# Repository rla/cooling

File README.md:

# avrcooling

PC cooling controller for rotary cooling devices (fans/pumps). It has
the following features:

 * Supports 4 cooling devices.
 * Can disable devices that still run on minimal PWM.
 * Monitors devices RPM.
 * RPM measurement supports pulse stretching.
 * Supports 2 thermal sensors.
 * Error signal output.
 * Can be controlled/queried over RS-232 interface.
 * Command-line client to query/debug/control the device.
 * Hardware design and source code is MIT-licensed.

### Control algorithm

The control algorithm uses 2 [decision tables](http://en.wikipedia.org/wiki/Decision_table),
one per thermal sensor. Table rows contain the following information:

 * enabled - whether the control row is enable.
 * min_temp - lower bound for activating the control row.
 * max_temp - upper bound for activating the control row.
 * affect_fan0 - whether to apply the row to fan 0.
 * affect_fan1 - whether to apply the row to fan 1.
 * affect_fan2 - whether to apply the row to fan 2.
 * affect_fan3 - whether to apply the row to fan 3.
 * fan0_pwm - PWM value to apply for fan 0.
 * fan1_pwm - PWM value to apply for fan 1.
 * fan2_pwm - PWM value to apply for fan 2.
 * fan3_pwm - PWM value to apply for fan 3.

There are 5 rows in each table. The first row with
min_temp...max_temp range including the current temperature is used for
applying the control values.

All cooling fans start initially in disabled state and with
0 PWM. When a fan PWM is set to a value greater than 0 then the fan power is
enabled. When PWM is set to 0 then the fan is also powered down.

Control table rows are checked periodically. The rows can be
read and updated using the command-line PC app described below.

## Project structure

The project is divided into 3 subdirectories:

 * `avr` - source for microcontroller binary.
 * `hw` - physical hardware design.
 * `pc` - NodeJS command-line app for communication.

## Hardware

### Pin allocation

 * pin  1: reset, connected to VCC and protected by zener diode
 * pin  2: USART RX line (pullup?)
 * pin  3: USART TX line
 * pin  4: PD2, Error signal output
 * pin  5: PD3, OC2B, fan 4 PWM output
 * pin  6: PD4, not connected
 * pin  7: VCC
 * pin  8: GND
 * pin  9: XTAL 1
 * pin 10: XTAL 2
 * pin 11: PD5, OC0B, fan 2 PWM output
 * pin 12: PD6, OC0A, fan 1 PWM output
 * pin 13: PD7, not connected
 * pin 14: PB0, fan 1 enable
 * pin 15: PB1, fan 2 enable
 * pin 16: PB2, fan 3 enable
 * pin 17: PB3, fan 3 PWM output
 * pin 18: PB4, fan 4 enable
 * pin 19: PB5, not connected
 * pin 20: AVCC, connected to VCC through low-pass filter L1/C13
 * pin 21: AREF, analog reference, decoupled with 100nF cap C10
 * pin 22: GND
 * pin 23: PC0, ADC0, temperature sensor 1 input, low-pass filter R5/C7
 * pin 24: PC1, ADC1, temperature sensor 2 input, low-pass filter R3/C8
 * pin 25: PC2, fan 1 RPM input, pull-up, low-pass filter R10/C9
 * pin 26: PC3, fan 2 RPM input, pull-up, low-pass filter R9/C11
 * pin 27: PC4, fan 3 RPM input, pull-up, low-pass filter R8/C12
 * pin 28: PC5, fan 4 RPM input, pull-up, low-pass filter R7/C14

### Port directions

#### Port B

 * PB0 - output (fan 1 enable)
 * PB1 - output (fan 2 enable)
 * PB2 - output (fan 3 enable)
 * PB3 - output (fan 3 PWM)
 * PB4 - output (fan 4 enable)
 * PB5 - output (not connected)
 * PB6 - output (overriden by xtal)
 * PB7 - output (overriden by xtal)

#### Port C

 * PC0 - input (ADC)
 * PC1 - input (ADC)
 * PC2 - input (fan 1 RPM, pull-up)
 * PC3 - input (fan 2 RPM, pull-up)
 * PC4 - input (fan 3 RPM, pull-up)
 * PC5 - input (fan 4 RPM, pull-up)
 * PC6 - input (default reset config)
 * PC7 - not in circuit/registry

#### Port D

 * PD0 - output (overriden by USART)
 * PD1 - output (overriden by USART)
 * PD2 - output (error)
 * PD3 - output (fan 4 PWM)
 * PD4 - output (not connected)
 * PD5 - output (fan 2 PWM)
 * PD6 - output (fan 1 PWM)
 * PD7 - output (not connected)

### Full schematics

Full schematics in Eagle format can be found in the file `hw/schematics.sch`.

#### Part list

 * C1 10uF/16V
 * C2 100nF/63V 5mm
 * C3, C4 22pF/63V 2.54mm
 * C5 100nF/63V 5mm
 * C6 10uF/16V 5mm
 * C7, C8 10nF/100V 5mm
 * C9, C11, C12, C14 10nF/63V 5mm
 * C10 100nF/63V 5mm
 * C13 100nF/63V 5mm
 * D1 5.1V zener 7.62mm
 * D2, D3, D4, D5 2N4007
 * IC1 Atmega88 DIP28
 * R1, R2, R3, R4, R5, R6, R7, R8, R9, R10, R11 10k
 * Q1 12MHz
 * Q2, Q4, Q6, Q8 2N7000
 * Q3, Q5, Q7, Q9 IRF9530
 * L1 10uH
 * X3 molex power connector, [Farnell product page](http://uk.farnell.com/jsp/search/productdetail.jsp?SKU=1391827)
 * X6, X7, X8, X9 molex 47053-1000 headers, [Farnell product page](http://uk.farnell.com/jsp/search/productdetail.jsp?SKU=2313705)

### Board layout

Board layout in Eagle format can be found in the file `hw/board.brd`. Layout
suitable for tone-transfer can be found in the PDF file `hw/board.pdf`.

Photo of 2 completed units:

### Fan connectors

4-wire connectors are standardized in the [specification](http://www.formfactors.org/developer%5Cspecs%5C4_Wire_PWM_Spec.pdf).
Connector pinout with typical wire colors is:

 * 1 - GND - black
 * 2 - 12V - yellow
 * 3 - RPM - green
 * 4 - PWM - blue

The max fan current is limited by switch MOSFET channel resistance in ON mode.
This is about 0.3 Ohms. Max dissipation of 1W gives the max current of about 1.9A.

#### 3-wire connectors

3-wire connectors lack PWM signal but are otherwise compatible with
4-wire headers. Pinout:

 * 1 - GND - black
 * 2 - 12V - red
 * 3 - RPM - yellow

While a 3-wire fan lacks PWM control, it can still be made variable-speed by
modulating the supply voltage. This can be implemented with the following
circuit:

#### Temp. sensor connectors

These connect MCP9700 to the board. There can be up to 2 sensors
connected. The system assumes 0.5V offset and 10mv per °C. This can be
changed by recompiling the firmware.

 * 1 - sensor output
 * 2 - sensor power (5V)
 * 3 - GND

#### Error signal connector

Error signal is set high whenever an enabled fan's RPM
reads 0. The signal comes directly from MCU and cannot
be directly loaded with higher current than 40mA.

 * 1 - error signal
 * 2 - GND

#### RS-232 interface

The RS-232 interface is used for updating the control line tables and
for debugging the device. The connector is denoted as X1 on schematics
and board and has the following pinout:

 * 1 - TX line
 * 2 - RX line
 * 3 - GND

A level translator has to be used for connecting the device to PC. PC
uses signal levels -12V/+12V while the device uses normal TTL levels 0V/5V.

A level translator can be built using the [MAX232](http://www.ti.com/lit/ds/symlink/max232.pdf)
chip or using a prebuilt module/cable/converter. There are various circuits and
building instructions on the Internet.

### Compiling firmware

The project contains a Makefile that includes build targets
with [avr-gcc](http://www.nongnu.org/avr-libc/) compiler.

To build the HEX binary for the controller:

    cd avr
    make

If [avrdude](http://www.nongnu.org/avrdude/) is installed then the hex file
can be burned into the device with the command:

    make burn

### Fuses

 * Clock: Full-swing crystal, BOD enabled
 * BOD 4.3V

#### Low fuse

 * CKDIV8 1 (unprogrammed)
 * CKOUT 1 (unprogrammed)
 * SUT1 0 (crystal, BOD enabled)
 * SUT0 1 (crystal, BOD enabled)
 * CKSEL3 0
 * CKSEL2 1
 * CKSEL1 1
 * CKSEL0 1

CKSEL is for full-swing crystal osc. lfuse total 11010111 = 0xd7.

#### High fuse

 * RSTDISBL 1 (unprogrammed)
 * DWEN 1 (unprogrammed)
 * SPIEN 0 (programmed)
 * WDTON 1 (unprogrammed)
 * EESAVE 1 (unprogrammed)
 * BODLEVEL2 1
 * BODLEVEL1 0
 * BODLEVEL0 0

hfuse total 11011100 = 0xdc.

If avrdude is installed then correct fuses can be burned
using the command:

    make burn-fuse

## Client

The client application is used for updating the control table lines
and for debugging the device.

Client options and supported commands:

```
Usage: avrcooling --port <port> --command <command> [arguments]
Recognized commands:
  disable0       disable fan 0
  disable1       disable fan 1
  disable2       disable fan 2
  disable3       disable fan 3
  echo           sends and receives the given byte
  enable0        enable fan 0
  enable1        enable fan 1
  enable2        enable fan 2
  enable3        enable fan 3
  nostretch0     disable pulse stretch for fan 0
  nostretch1     disable pulse stretch for fan 1
  nostretch2     disable pulse stretch for fan 2
  nostretch3     disable pulse stretch for fan 3
  pwm0_get       query fan 0 PWM level (0-255)
  pwm0_set       set fan 0 PWM (0-255)
  pwm1_get       query fan 1 PWM level (0-255)
  pwm1_set       set fan 1 PWM (0-255)
  pwm2_get       query fan 2 PWM level (0-255)
  pwm2_set       set fan 2 PWM (0-255)
  pwm3_get       query fan 3 PWM level (0-255)
  pwm3_set       set fan 3 PWM (0-255)
  rpm0           query fan 0 RPM
  rpm1           query fan 1 RPM
  rpm2           query fan 2 RPM
  rpm3           query fan 3 RPM
  stretch0       enable pulse stretch for fan 0
  stretch1       enable pulse stretch for fan 1
  stretch2       enable pulse stretch for fan 2
  stretch3       enable pulse stretch for fan 3
  stretch_info   query pulse stretch settings
  temp0          query sensor 0 temperature
  temp0_line_get get control table line (0-4) for sensor 0
  temp0_line_set set control table line (0-4) for sensor 0
  temp1          query sensor 1 temperature
  temp1_line_get get control table line (0-4) for sensor 1
  temp1_line_set set control table line (0-4) for sensor 1

```

### Debugging

Set environment variable `DEBUG=*` and run the command.

    DEBUG=* avrcooling ...

### Installation

Assuming that you have [NodeJS](https://nodejs.org/) installed:

    npm install -g avrcooling

### Protocol

The client-device communication protocol terminates messages with line ends.
Data on individual lines is encoded in the hex encoding.

Decoded commands have the following format:

    [command_byte, arguments..., checksum_byte]

Responses have the following format:

    [response_ok, response arguments..., checksum_byte]

or

    [response_fail, checksum_byte]

or

    [command_checksum_fail, checksum_byte]

Multibyte integers are sent in big-endian format. Maximum decoded message length is 10 bytes.
The detailed description of the protocol is found in [pc/lib/commands.js](pc/lib/commands.js).

The checksum computation uses the Pearson hash algorithm:
<http://en.wikipedia.org/wiki/Pearson_hashing>. The constants
table can be found in [avr/src/pearson.c](avr/src/pearson.c).

## Changelog

 * 2018-11-11 Do not reset PWM on disable. Implement missing get-pwm command.
   Reset RPM only on timeout preventing sporadic 0 RPM responses. Update RPM
   atomically preventing potentially corrupted responses due to data race.
 * 2016-01-31 BOD (brown-out detection) enabled.
 * 2015-03-24 Pulse stretching is implemented. Client code is finished.
 * 2014-07-27 Client code is mostly working.
 * 2014-07-17 AVR code is mostly working.
 * 2014-02-01 Physical hardware design is ready.

## Known issues

 * Max ADC input voltage is 1.1V when the internal reference is selected (by default).
 * Temperature sensor MCP9700 needs 100nF decoupling cap at the sensor to ensure
   stable operation.

## License

The MIT License. See the LICENSE file.

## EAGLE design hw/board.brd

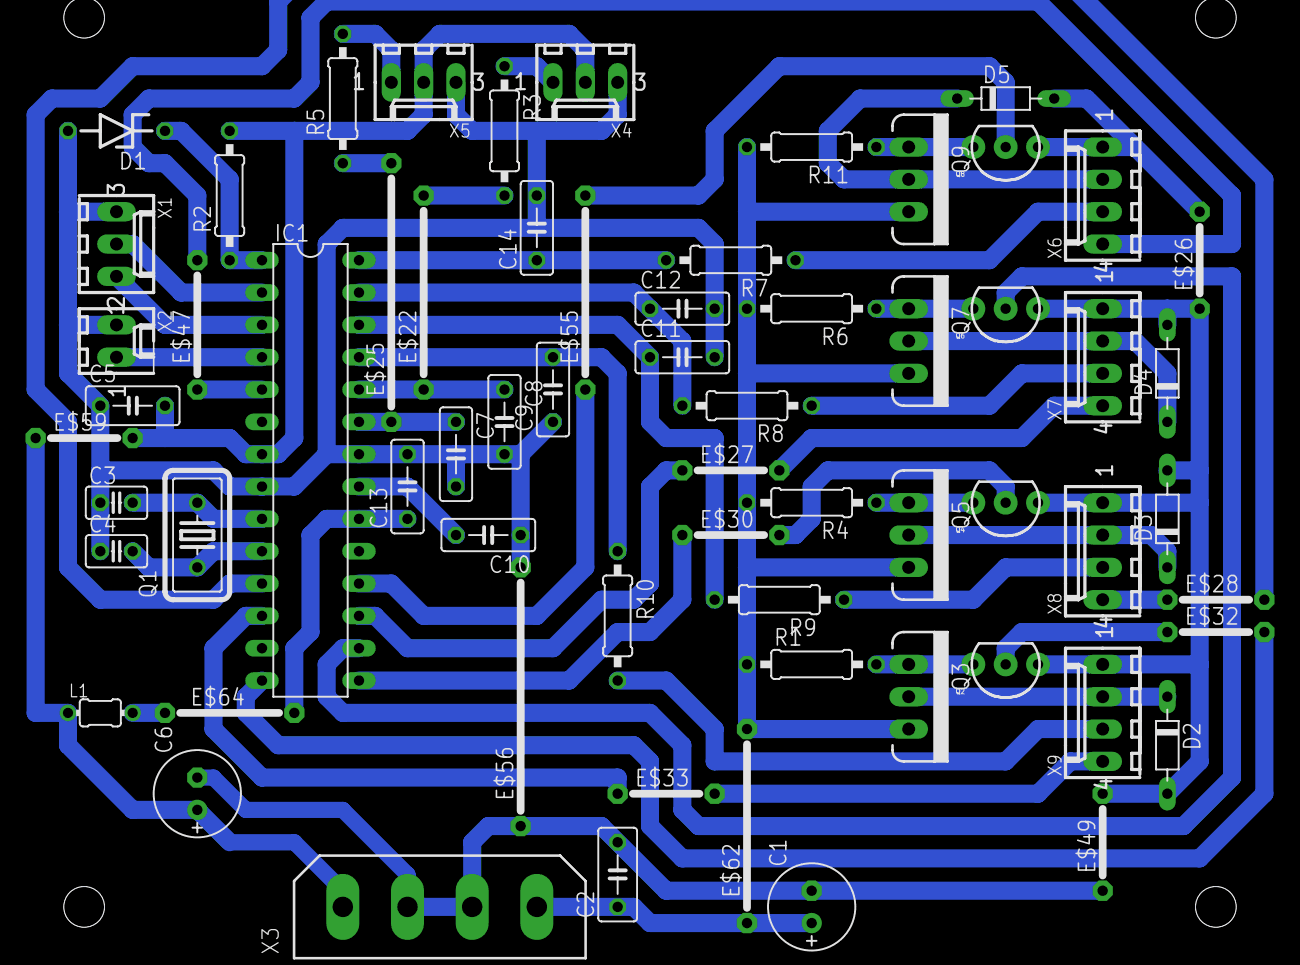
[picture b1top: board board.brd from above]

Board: 2 copper layers, 65 parts (0 on the bottom side), 35 nets.

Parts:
C1, C6: E2,5-7
C2, C5: C050-030X075
C3, C4: C025-025X050
C7, C8, C9, C10, C11, C12, C13, C14: C050-025X075
D1: ZDIO-7.5
D2, D3, D4, D5: D-7.5
E$22, E$55, E$62: 15
E$25, E$56: 20
E$26, E$27, E$28, E$30, E$32, E$33, E$49, E$59: 07
E$47, E$64: 10
IC1: DIL28-3
L1: LAL02
Q1: HC18U-V
Q2, Q4, Q6, Q8: TO-92-AMMO
Q3, Q5, Q7, Q9: TO220V
R1, R2, R3, R4, R5, R6, R7, R8, R9, R10, R11: 0207/10
X1, X4, X5: 6410-03
X2: 6410-02
X3: 9090-4V
X6, X7, X8, X9: 6410-04

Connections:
S$1: D2.A, D3.A, D4.A, E$49.2, Q2.1, Q4.1, Q6.1, X7.1, X8.1, X9.1
S$2: D5.C, Q9.2, X6.2
S$3: D4.C, Q7.2, X7.2
S$4: D3.C, Q5.2, X8.2
S$5: D2.C, Q3.2, X9.2
S$6: E$62.2, Q3.3, Q5.3, Q7.3, Q9.3, R1.1, R4.2, R6.2, R11.2
S$8: Q2.3, Q3.1, R1.2
S$9: C11.1, R9.2
S$10: Q6.3, Q7.1, R6.1
S$11: Q8.3, Q9.1, R11.1
S$12: R7.1, X6.3
S$13: R8.1, X7.3
S$14: R9.1, X8.3
S$15: R10.2, X9.3
S$16: C12.1, R8.2
S$17: E$32.1, Q2.2
S$18: C9.2, R10.1
S$20: C5.2, E$59.2, R2.2, X4.2, X5.2
S$22: E$47.2, X6.4
S$24: E$55.2, Q8.2
S$30: E$28.1, X8.4
S$31: C3.1, C4.1, C7.2, C8.2, C9.1, C10.1, C11.2, C12.2, D1.A, E$56.2, X1.3, X2.2, X4.3, X5.3
S$33: D5.A, Q8.1, X6.1
S$34: C13.1, E$64.2
S$38: C3.2, Q1.2
S$39: D1.C, R2.1
S$40: C4.2, Q1.1
S$41: E$22.2, R3.2
S$42: C1.+, E$62.1, X3.4
S$43: R5.2, X5.1
S$45: E$59.1, L1.1, X3.1
S$46: Q4.3, Q5.1, R4.1
S$48: R3.1, X4.1
S$51: C6.-, E$49.1, E$56.1, X3.2, X3.3
S$57: E$64.1, L1.2

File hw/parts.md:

# Parts

 * C1 10uF/16V
 * C2 100nF/63V 5mm
 * C3, C4 22pF/63V 2.54mm
 * C5 100nF/63V 5mm TODO
 * C6 10uF/16V 5mm
 * C7, C8 10nF/100V 5mm
 * C9, C11, C12, C14 10nF/63V 5mm
 * C10 100nF/63V 5mm
 * C13 100nF/63V 5mm
 * D1 5.1V zener 7.62mm
 * D2, D3, D4, D5 2N4007
 * IC1 Atmega88 DIP28
 * R1, R2, R3, R4, R5, R6, R7, R8, R9, R10, R11 10k
 * Q1 12MHz
 * Q2, Q4, Q6, Q8 2N7000
 * Q3, Q5, Q7, Q9 IRF9530
 * L1 10uF

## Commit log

2014-04-24 Last updates
2014-07-14 Description of MCU pins, ports and used registers
2014-07-14 Refactor some of the source code
2014-07-17 Lots of new features
2014-07-17 Refactor: rename folders
2014-07-17 Clean up the project root
2014-07-17 Describe features and add license file
2014-07-17 Move source into separate directory
2014-07-17 Move documentation to readme
2014-07-17 Communication protocol specified, checksums work
2014-07-27 Client side node app/package package.json file
2014-07-27 Init timer 2 for fan 2 and 3 PWM
2014-07-27 Clean up communication responses
2014-07-27 Client side command-line app supports basic commands
2014-07-27 Remove old testing files
2014-07-27 Mention NodeJS library and command-line client
2014-07-30 Primitive adjustment algorithm, error setting, fan init
2014-08-01 Fan connector description
2014-11-26 Decision tables for control algorithm
2015-03-19 Refactored the command-line client
2015-03-19 Control line output as JSON
2015-03-22 Initial support for pulse stretching
2015-03-22 AVR side of protocol for enabling/disabling pulse stretch
2015-03-22 Make ECHO command response respect standard command format, closes #1
2015-03-22 Add return after writing RESPONSE_FAIL, closes #2
2015-03-23 Init fans with 0 PWM
2015-03-23 0-based indexing for sensor/fan naming
2015-03-23 Add unset_error and take down the error flag when all enabled fans have RPM reading, closes #3
2015-03-23 Pulse stretch command implemented for client
2015-03-24 Make --help output nicer and command naming consistent, closes #4
2015-03-24 Rename the client package
2015-03-24 Enhanced client package.json
2015-03-24 Update documentation
2015-03-24 Rename the project
2015-03-24 Support command-line usage
2015-03-24 Remove trailing comma
2015-03-24 Fix the main file name (.js missing at the end)
2015-03-24 Add shebang wrapper
2015-03-25 Add 3-wire to 4-wire adapter
2015-03-25 Link to avrdude
2015-03-27 Use 0-based property naming in control row encode/decode objects
2015-03-27 Control algorithm description
2015-03-27 Update control algorithm description
2015-04-02 Added photo of completed hardware
2015-04-02 Describe error output and temp. sensor inputs
2016-01-30 Upgrade serialport version
2016-01-30 Bump version
2016-01-31 New fuses+documentation
2016-01-31 Typo in changelog
2018-11-11 Reset RPM only on timeout.
    This prevents sporadic 0 RPM responses.
2018-11-11 Implement missing get-pwm command.
2018-11-11 Do not reset PWM on disable.
    Removes surprising and undocumented behavior.
2018-11-15 Update RPM atomically.
2018-11-19 Add missing ground connection to output MOSFET switches
2018-11-19 Regenerate schematics PNG file

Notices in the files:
parts and their libraries:
sparkfun-discretesemi: Licensing: CC v3.0 Share-Alike You are welcome to use this library for commercial purposes.
